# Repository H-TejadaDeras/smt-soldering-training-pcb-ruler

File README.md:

# smt-soldering-training-pcb-ruler
SMT Soldering I and II Training PCB Ruler. Made for the Olin College Machine Shop. Loosely based on the UIUC PCB Ruler (https://github.com/nebhrajani-a/uiuc-pcb-ruler).

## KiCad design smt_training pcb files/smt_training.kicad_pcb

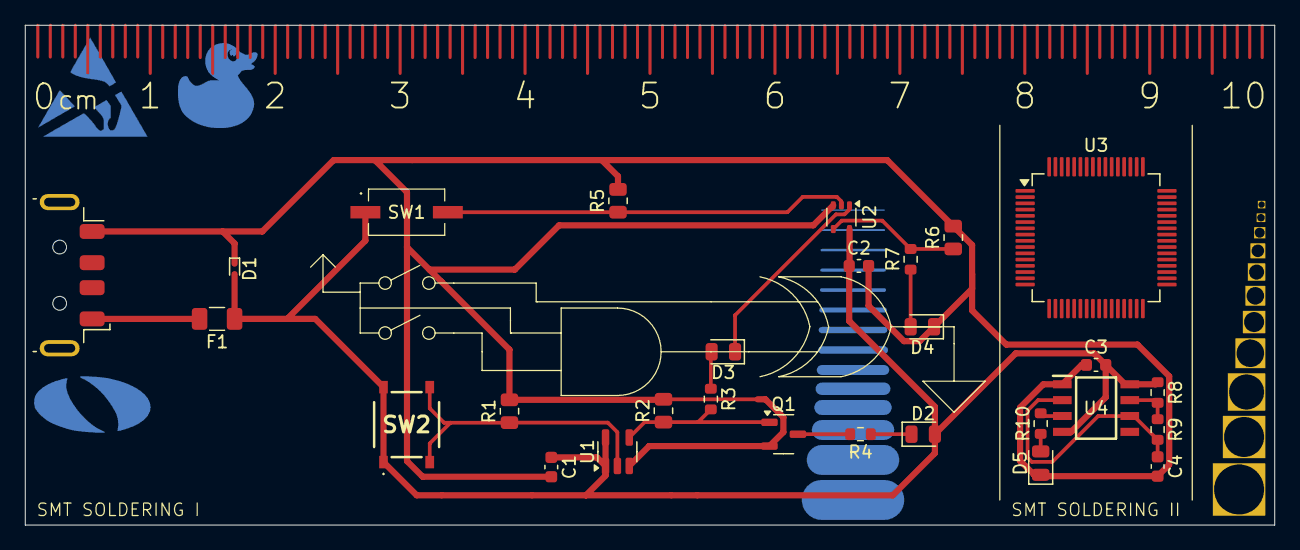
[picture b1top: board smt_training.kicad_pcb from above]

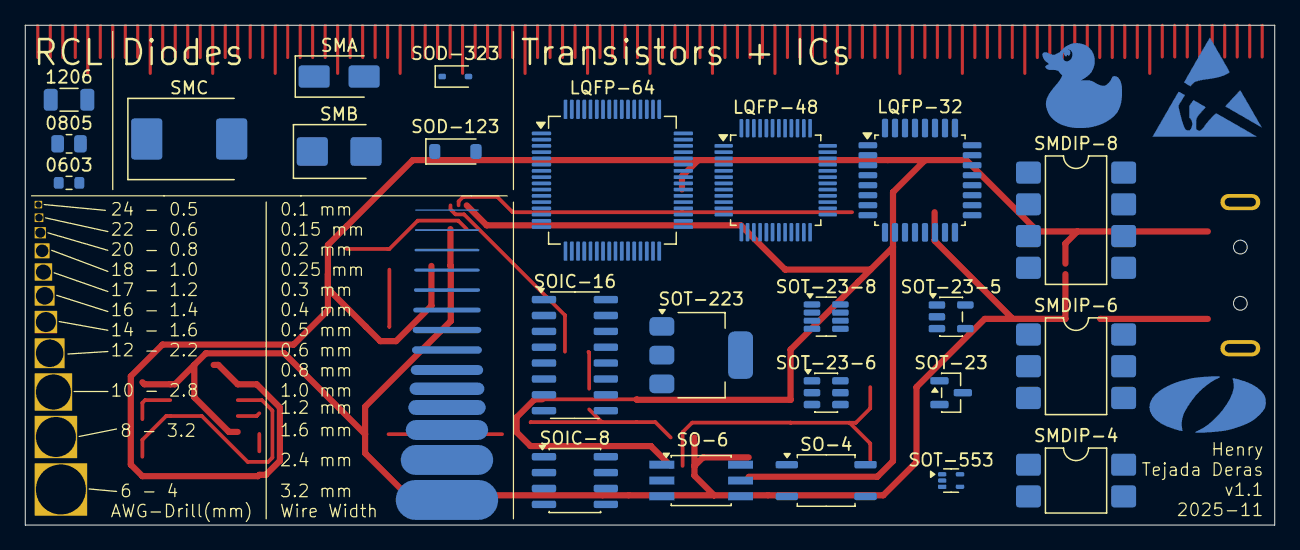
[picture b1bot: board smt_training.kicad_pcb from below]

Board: 2 copper layers, 100.0 x 40.0 mm, 52 parts (24 on the bottom side), 16 nets.

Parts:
0603: R_0603_1608Metric
0805: R_0805_2012Metric
1206: R_1206_3216Metric
C1, C2: 0.1u; C_0603_1608Metric
C3: 0.01u; C_0603_1608Metric
C4: 1u; C_0603_1608Metric
D1: DF2S5.6FS,L3M; D_SOD-923
D2, D3, D4, D5: LED; LED_0805_2012Metric
F1: 250m; Fuse_1206_3216Metric
J1: AU-Y1006-2; USB_A_Molex_48037-2200_Horizontal
LQFP-32: LQFP-32_7x7mm_P0.8mm
LQFP-48: LQFP-48_7x7mm_P0.5mm
LQFP-64: LQFP-64_10x10mm_P0.5mm
Q1: 2N7002-7-F; SOT-23-3
R1, R2, R5, R6: 10K; R_0805_2012Metric
R3, R4, R7, R10: 200; R_0603_1608Metric
R8, R9: 500k; R_0603_1608Metric
SMA: D_SMA
SMB: D_SMB
SMC: D_SMC
SMDIP-4: SMDIP-4_W7.62mm
SMDIP-6: SMDIP-6_W7.62mm
SMDIP-8: SMDIP-8_W7.62mm
SO-4: SO-4_4.4x3.9mm_P2.54mm
SO-6: SO-6_4.4x3.6mm_P1.27mm
SOD-123: D_SOD-123
SOD-323: D_SOD-323
SOIC-8: SOIC-8_3.9x4.9mm_P1.27mm
SOIC-16: SOIC-16_3.9x9.9mm_P1.27mm
SOT-23: SOT-23
SOT-23-5: SOT-23-5
SOT-23-6: SOT-23-6
SOT-23-8: SOT-23-8
SOT-223: SOT-223
SOT-553: SOT-553
SW1: PTS636SK25FSMTR LFS; PTS636SK25FSMTRLFS
SW2: PTS526SM15SMTR2 LFS; PTS526SM15SMTR2LFS
U1: SN74LVC1G08DBVR; SOT-23-5
U2: SN74LVC1G86DCKR; SOT-353_SC-70-5
U3: LQFP64 IC; LQFP-64_10x10mm_P0.5mm
U4: NE555S-13; SOIC127P600X170-8N

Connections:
+5V: C1.1, C2.1, C3.2, D1.2 (A2), D2.2 (A), F1.1, R8.1, SW1.1 (A), SW2.1, SW2.2, U1.1, U1.5 (VCC), U2.5 (VCC), U4.4 (RESET), U4.8 (VCC)
/DISCH: R8.2, R9.1, U4.7 (DISCH)
/THRES: C4.1, R9.2, U4.2 (TRIG), U4.6 (THRES)
GND: C1.2, C2.2, C3.1, C4.2, D1.1 (A1), D4.1 (K), D5.1 (K), J1.4 (GND), Q1.2 (S), R1.2, R2.2, R5.2, R6.2, U1.3 (GND), U2.3 (GND), U4.1 (GND)
unnamed: D2.1 (K), R4.1
unnamed: D3.2 (A), R3.1
unnamed: D3.1 (K), U2.1
unnamed: D4.2 (A), R7.1
unnamed: D5.2 (A), R10.1
unnamed: F1.2, J1.1 (VBUS)
unnamed: Q1.3 (D), R4.2
unnamed: Q1.1 (G), R2.1, R3.2, U1.4
unnamed: R1.1, SW2.3, SW2.4, U1.2
unnamed: R6.1, R7.2, U2.4
unnamed: R5.1, SW1.2 (B), U2.2
unnamed: R10.2, U4.3 (OUT)

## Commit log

2025-11-25 Added PCB Ruler v1 Files
2025-11-26 Fixed Bypassed SW2; Added Soldermask to Back Icons; Updated Version Number
2025-11-26 Added Fabrication Gerber Files for Ruler v1.1
